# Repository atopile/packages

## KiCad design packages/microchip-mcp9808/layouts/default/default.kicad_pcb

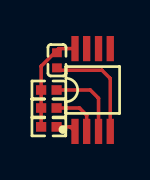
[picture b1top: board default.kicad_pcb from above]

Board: 2 copper layers, 5 parts (0 on the bottom side), 5 nets.

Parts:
C1: 1±10.0%F; C0402
R1, R2, R3: 10000±1.0%Ω; R0402
U1: MSOP-8_L3.0-W3.0-P0.65-LS4.9-BL

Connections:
Alert: R1.2, U1.3
SCL: R2.2, U1.2
SDA: R3.2, U1.1
hv: C1.1, R1.1, R2.1, R3.1, U1.8
lv: C1.2, U1.4, U1.5, U1.6, U1.7

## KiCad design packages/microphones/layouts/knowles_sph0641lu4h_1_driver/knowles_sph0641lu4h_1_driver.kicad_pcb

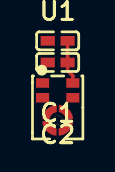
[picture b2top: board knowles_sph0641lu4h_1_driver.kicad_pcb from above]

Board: 2 copper layers, 3 parts (0 on the bottom side), 2 nets.

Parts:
C1: 100nF ±10% 16V X7R; C0402
C2: 220pF ±10% 50V X7R; C0402
U1: MIC-SMD_5P_L3.5-W2.7-P0.82_SPH0641LU4H-1

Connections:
VDD: C1.1, C2.1, U1.5
gnd: C1.2, C2.2, U1.3

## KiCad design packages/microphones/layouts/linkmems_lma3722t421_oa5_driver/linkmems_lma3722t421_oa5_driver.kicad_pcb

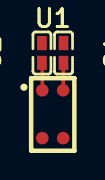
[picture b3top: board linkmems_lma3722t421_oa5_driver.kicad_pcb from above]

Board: 2 copper layers, 3 parts (0 on the bottom side), 3 nets.

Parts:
C1: 10µF ±20% 6.3V X5R; C0402
C2: 100nF ±10% 16V X7R; C0402
U1: MIC-SMD_4P-L3.8-W2.3-P2.66-TL

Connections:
OUT: C1.2, U1.1
VDD: C2.1, U1.2
gnd: C2.2, U1.3, U1.4
